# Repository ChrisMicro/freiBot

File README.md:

# freiBot
The freiBot is a very low cost two wheel robot.
The design goal is a robot which is
- easy and fast to build ( 6 hours )
- easy to program ( using an ARDUINO NANO )
- low circuit cost
- usefull for workshops

Here you can see the pictures:

http://roboterclub-freiburg.de/projekte/freibot

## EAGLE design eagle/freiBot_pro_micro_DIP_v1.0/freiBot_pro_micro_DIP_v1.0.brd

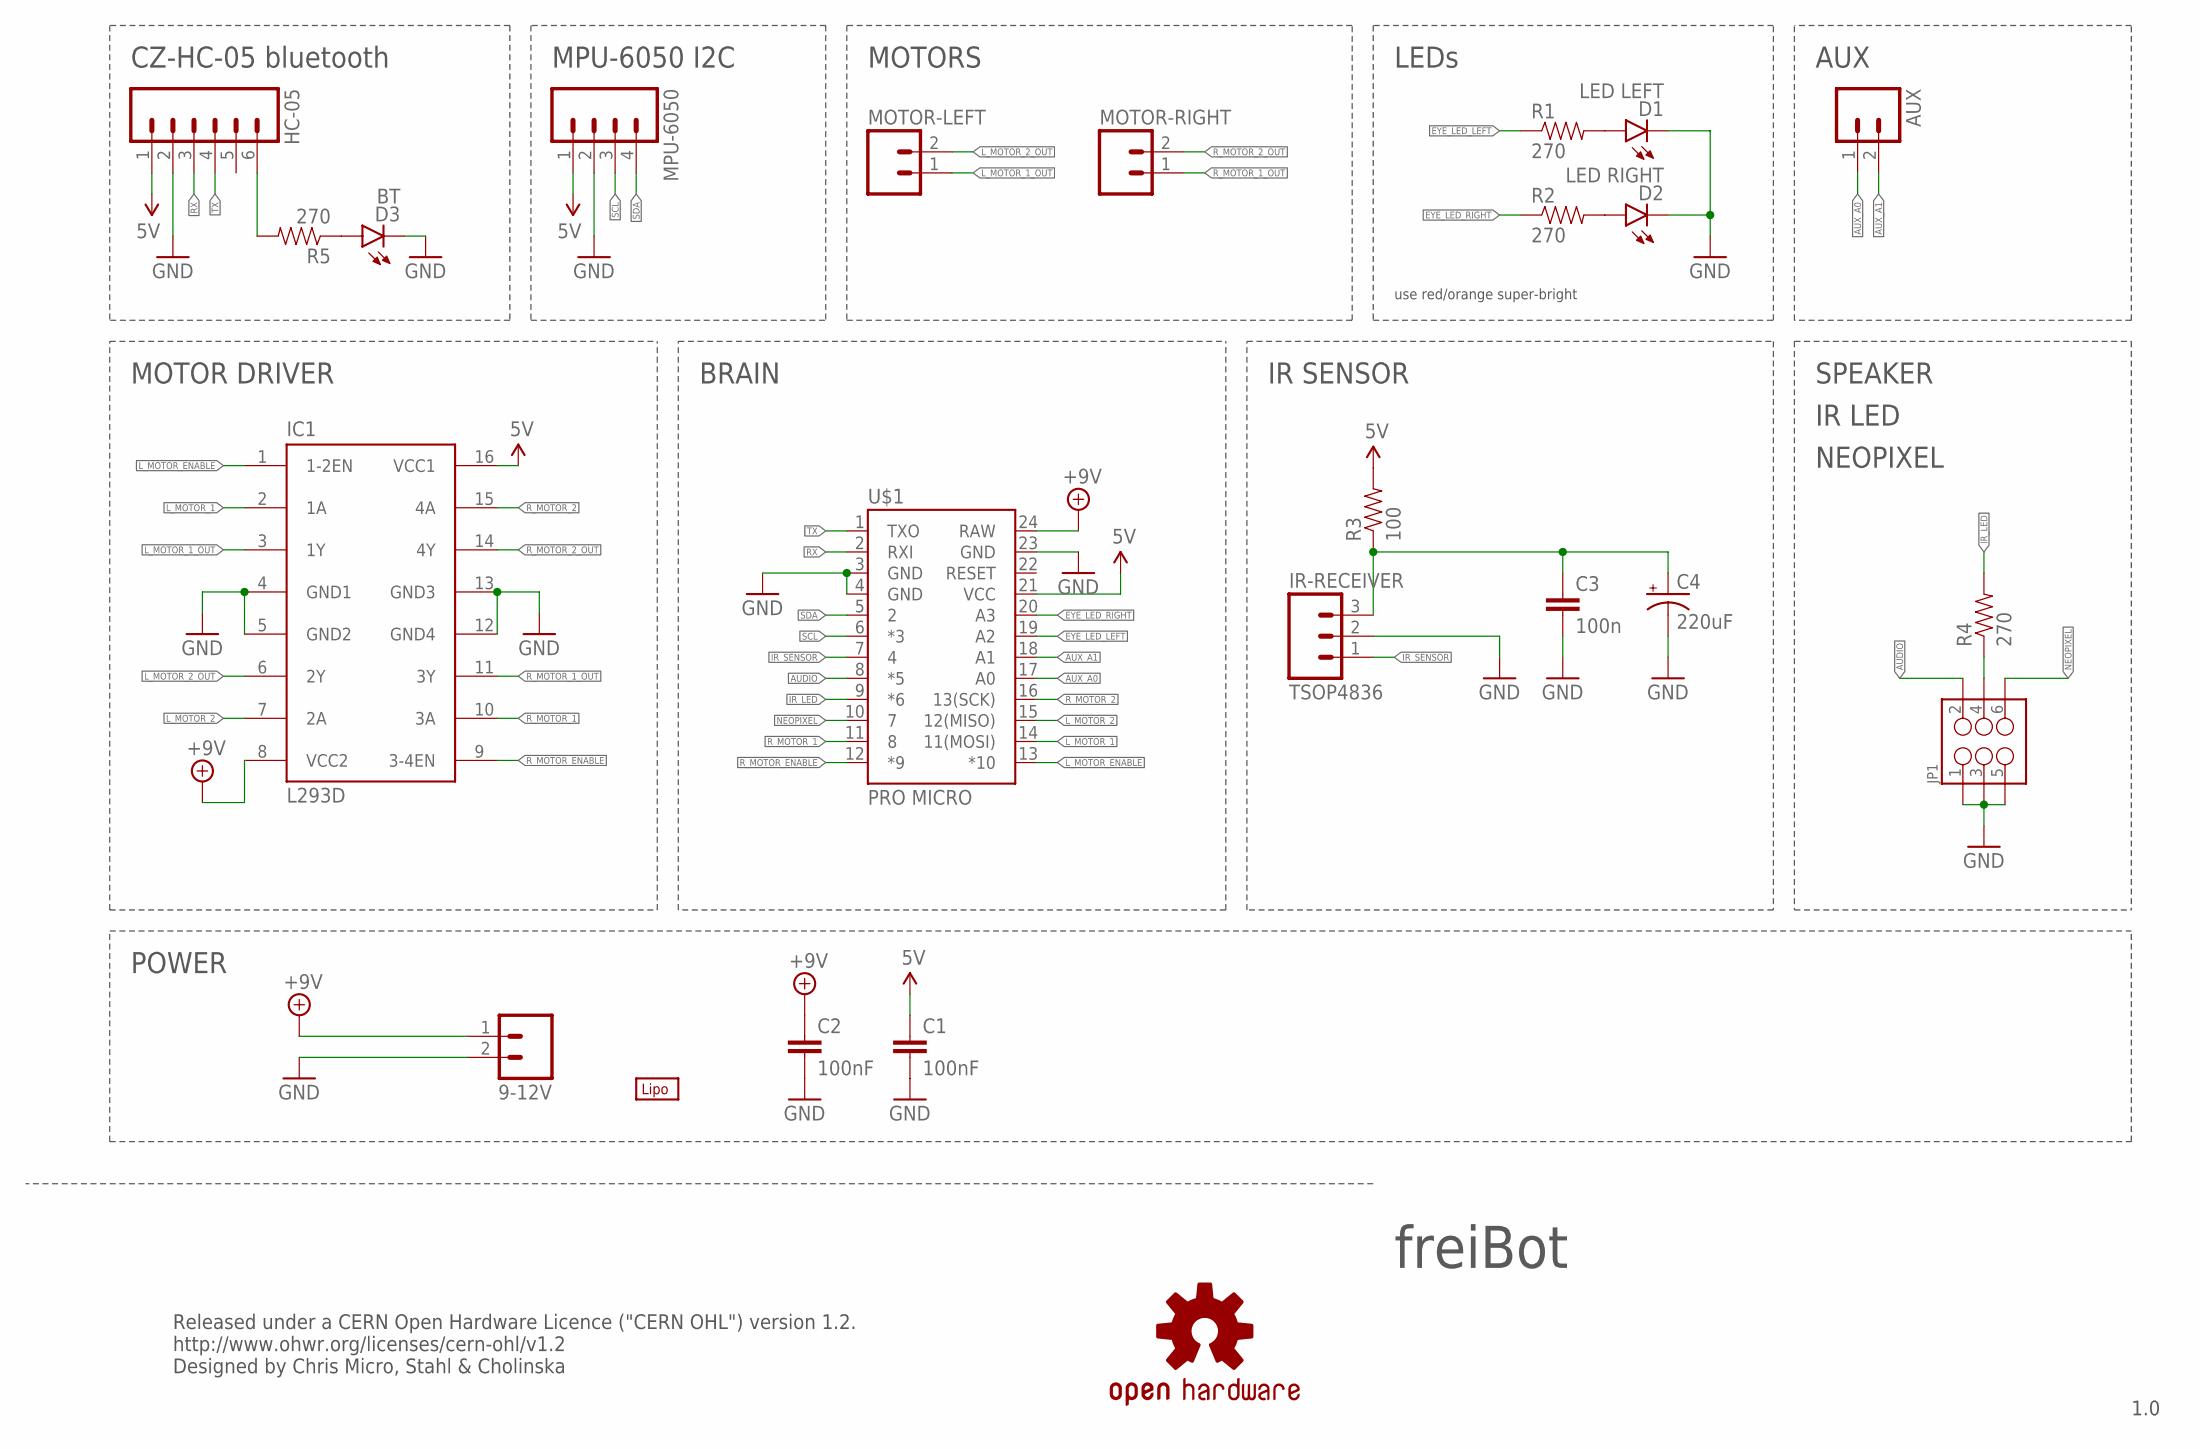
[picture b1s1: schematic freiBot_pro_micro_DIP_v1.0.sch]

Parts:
9-12V: M025MM; SCREWTERMINAL-5MM-2
AUX: M02LOCK_LONGPADS; 1X02_LOCK_LONGPADS
C1, C2: 100nF; CAP-PTH-SMALL-KIT
C3: 100n; CAP-PTH-SMALL-KIT
C4: 220uF; CPOL-RADIAL-100UF-25V
D1: LED LEFT; LED3MM
D2: LED RIGHT; LED3MM
D3: BT; LED3MM
HC-05: M06LONGPADS; 1X06_LONGPADS
IC1: L293D; DIL16
IR-RECEIVER: TSOP4836; 1X03_LONGPADS
JP1: M03X2NO_SILK; 2X3-NS
LOGO1: OSHW-LOGOL-COPPER; OSHW-LOGO-L_COPPER
MOTOR-LEFT: M025MM; SCREWTERMINAL-5MM-2
MOTOR-RIGHT: M025MM; SCREWTERMINAL-5MM-2
MPU-6050: M04LONGPADS; 1X04_LONGPADS
R1, R2, R4, R5: 270; AXIAL-0.3-KIT
R3: 100; AXIAL-0.3-KIT
U$1: PRO MICRO; ARDUINO_PRO_MICRO
U$2: LIPO-OUTLINE2000; LIPO-2000

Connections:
5V: C1.1, HC-05.1, IC1.16 (VCC1), MPU-6050.1, R3.P$2 (2), U$1.21 (VCC)
+9V: 9-12V.1, C2.1, IC1.8 (VCC2), U$1.24 (RAW)
AUDIO: JP1.2, U$1.8 (*5)
AUX_A0: AUX.1, U$1.17 (A0)
AUX_A1: AUX.2, U$1.18 (A1)
EYE_LED_LEFT: R1.P$1 (1), U$1.19 (A2)
EYE_LED_RIGHT: R2.P$1 (1), U$1.20 (A3)
GND: 9-12V.2, C1.2, C2.2, C3.2, C4.2 (-), D1.K (C), D2.K (C), D3.K (C), HC-05.2, IC1.4 (GND1), IC1.5 (GND2), IC1.12 (GND4), IC1.13 (GND3), IR-RECEIVER.2, JP1.1, JP1.3, JP1.5, MPU-6050.2, U$1.3 (GND), U$1.4 (GND), U$1.23 (GND)
IR_LED: R4.P$2 (2), U$1.9 (*6)
IR_SENSOR: IR-RECEIVER.1, U$1.7 (4)
L_MOTOR_1: IC1.2 (1A), U$1.14 (11(MOSI))
L_MOTOR_1_OUT: IC1.3 (1Y), MOTOR-LEFT.1
L_MOTOR_2: IC1.7 (2A), U$1.15 (12(MISO))
L_MOTOR_2_OUT: IC1.6 (2Y), MOTOR-LEFT.2
L_MOTOR_ENABLE: IC1.1 (1-2EN), U$1.13 (*10)
unnamed: D1.A, R1.P$2 (2)
unnamed: D2.A, R2.P$2 (2)
unnamed: D3.A, R5.P$1 (1)
unnamed: JP1.4, R4.P$1 (1)
unnamed: HC-05.6, R5.P$2 (2)
unnamed: C3.1, C4.1 (+), IR-RECEIVER.3, R3.P$1 (1)
NEOPIXEL: JP1.6, U$1.10 (7)
RX: HC-05.3, U$1.2 (RXI)
R_MOTOR_1: IC1.10 (3A), U$1.11 (8)
R_MOTOR_1_OUT: IC1.11 (3Y), MOTOR-RIGHT.1
R_MOTOR_2: IC1.15 (4A), U$1.16 (13(SCK))
R_MOTOR_2_OUT: IC1.14 (4Y), MOTOR-RIGHT.2
R_MOTOR_ENABLE: IC1.9 (3-4EN), U$1.12 (*9)
SCL: MPU-6050.3, U$1.6 (*3)
SDA: MPU-6050.4, U$1.5 (2)
TX: HC-05.4, U$1.1 (TXO)

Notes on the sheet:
IR SENSOR
LEDs
MOTORS
MPU-6050 I2C
MOTOR DRIVER
BRAIN
CZ-HC-05 bluetooth
NEOPIXEL
freiBot
POWER
AUX
SPEAKER
Released under a CERN Open Hardware Licence ("CERN OHL") version 1.2. http://www.ohwr.org/licenses/cern-ohl/v1.2 Designed by Chris Micro, Stahl & Cholinska
1.0
IR LED
use red/orange super-bright

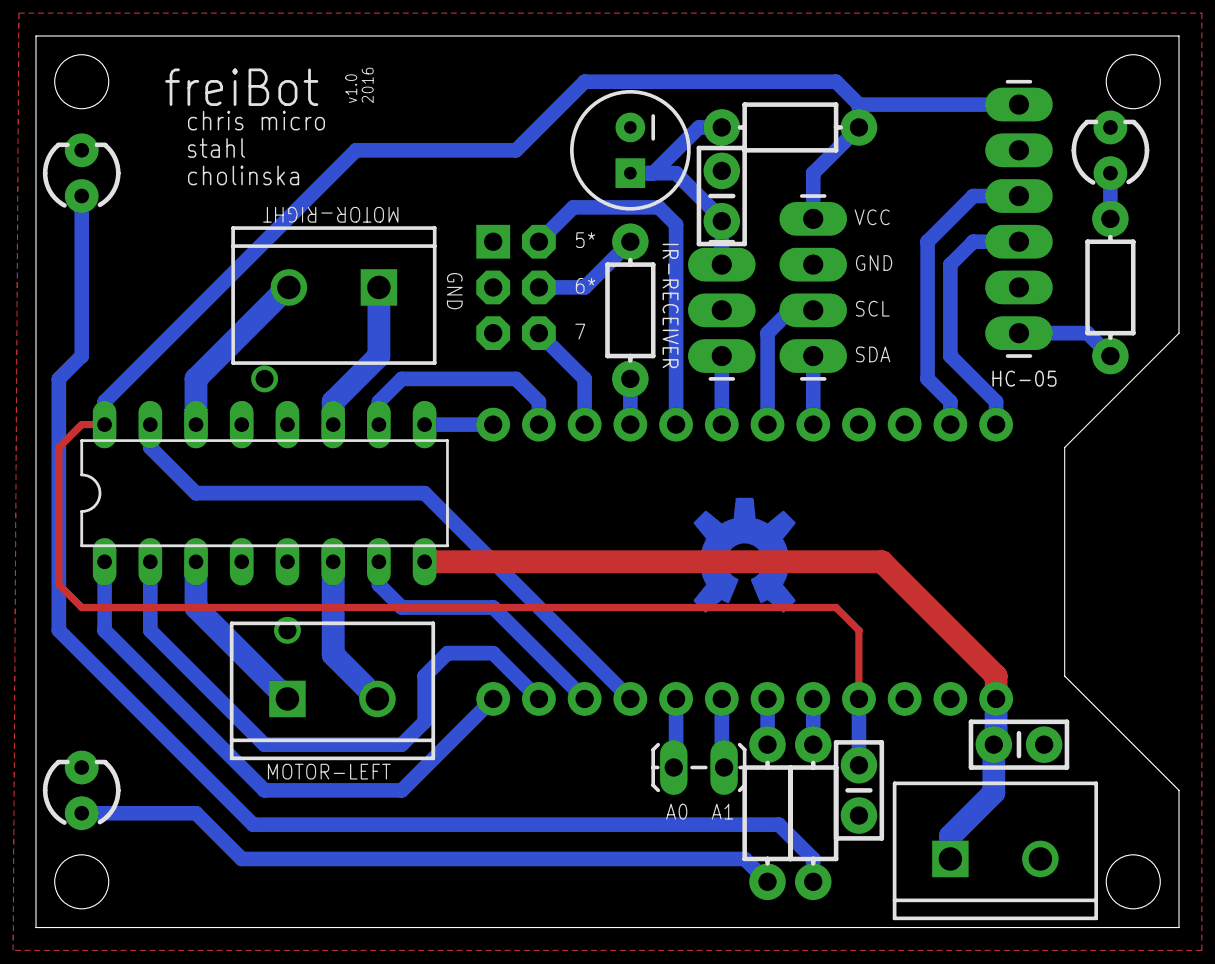
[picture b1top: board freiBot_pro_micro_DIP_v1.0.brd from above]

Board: 2 copper layers, 63.5 x 49.5 mm, 24 parts (1 on the bottom side), 31 nets.

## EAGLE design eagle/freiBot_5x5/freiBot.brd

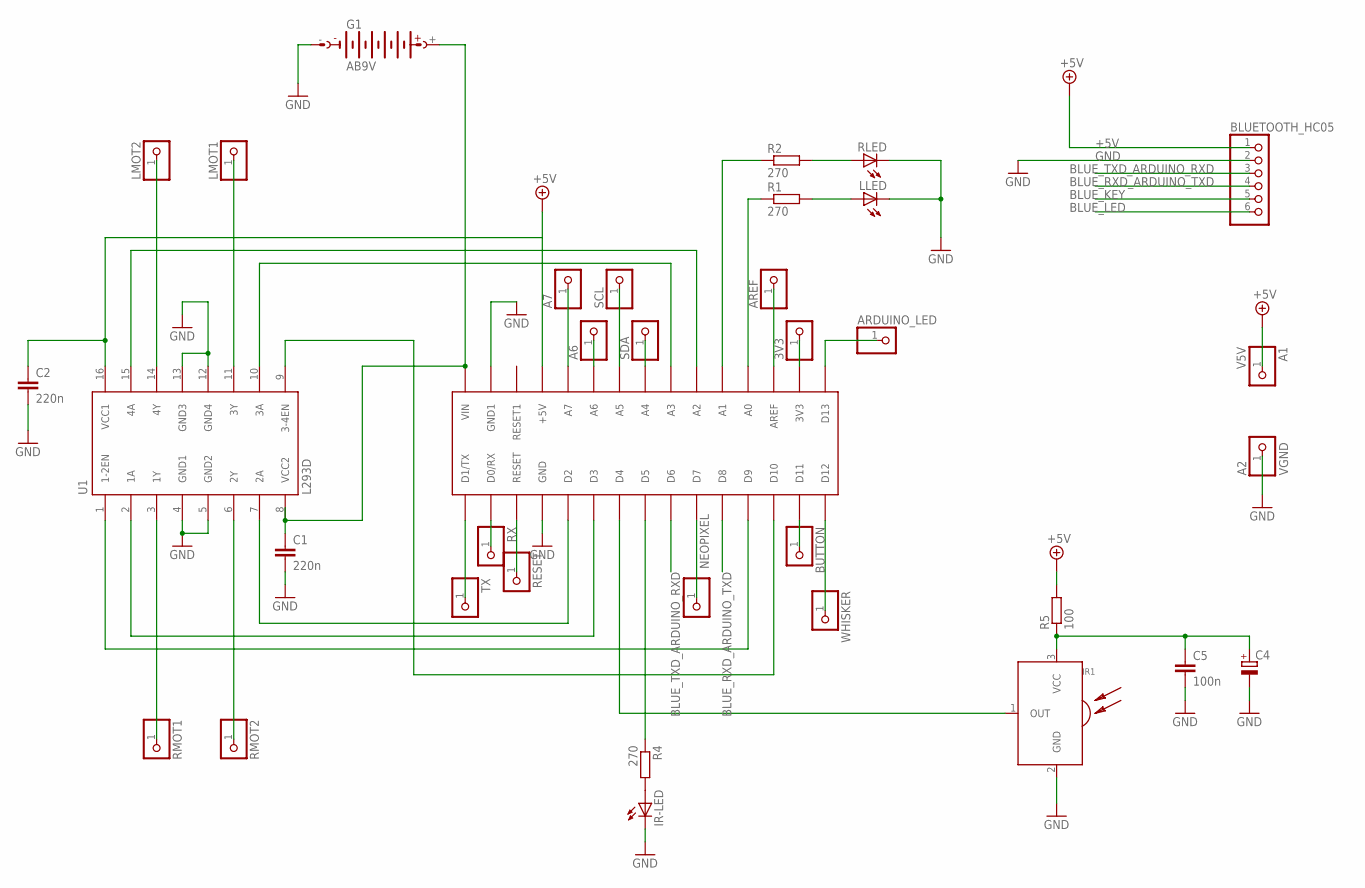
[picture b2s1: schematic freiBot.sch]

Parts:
3V3: PINHD-1X1; 1X01
A1: V5V; 1X01
A2: VGND; 1X01
A6, A7: PINHD-1X1; 1X01
ARDUINO_LED: PINHD-1X1; 1X01
AREF: PINHD-1X1; 1X01
BLUETOOTH_HC05: PINHD-1X6; 1X06
BUTTON: PINHD-1X1; 1X01
C1, C2: 220n; C075-042X103
C4: CPOL-EUE5-8.5; E5-8,5
C5: 100n; C050-025X075
G1: AB9V
IR1: SFH5110; SFH511*
IR-LED: LED5MM
LLED: LED10MM
LMOT1, LMOT2: PINHD-1X1; 1X01
NEOPIXEL: PINHD-1X1; 1X01
R1, R2, R4: 270; 0309/12
R5: 100; 0309/10
RESET: PINHD-1X1; 1X01
RLED: LED10MM
RMOT1, RMOT2: PINHD-1X1; 1X01
RX: PINHD-1X1; 1X01
SCL: PINHD-1X1; 1X01
SDA: PINHD-1X1; 1X01
TX: PINHD-1X1; 1X01
U1: L293D; DIL16
U2: ARDUINONANO; PDIP-32
WHISKER: PINHD-1X1; 1X01

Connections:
+5V: A1.1, BLUETOOTH_HC05.1, C2.1, R5.2, U1.16 (VCC1), U2.+5V
BLUE_KEY: BLUETOOTH_HC05.5
BLUE_LED: BLUETOOTH_HC05.6
BLUE_RXD_ARDUINO_TXD: BLUETOOTH_HC05.4, U2.D8
BLUE_TXD_ARDUINO_RXD: BLUETOOTH_HC05.3, U2.D6
GND: A2.1, BLUETOOTH_HC05.2, C1.2, C2.2, C4.-, C5.2, G1.-, IR1.2 (GND), IR-LED.K (C), LLED.K (C), RLED.K (C), U1.4 (GND1), U1.5 (GND2), U1.12 (GND4), U1.13 (GND3), U2.GND, U2.GND1
unnamed: U1.7 (2A), U2.D2
unnamed: U1.2 (1A), U2.D3
unnamed: U1.1 (1-2EN), U2.D9
unnamed: RMOT1.1, U1.3 (1Y)
unnamed: U1.9 (3-4EN), U2.D10
unnamed: U1.10 (3A), U2.A3
unnamed: U1.15 (4A), U2.A2
unnamed: RMOT2.1, U1.6 (2Y)
unnamed: LMOT1.1, U1.11 (3Y)
unnamed: LMOT2.1, U1.14 (4Y)
unnamed: C1.1, G1.+, U1.8 (VCC2), U2.VIN
unnamed: IR-LED.A, R4.2
unnamed: R1.1, U2.A0
unnamed: R2.1, U2.A1
unnamed: R2.2, RLED.A
unnamed: LLED.A, R1.2
unnamed: SDA.1, U2.A4
unnamed: SCL.1, U2.A5
unnamed: ARDUINO_LED.1, U2.D13
unnamed: U2.D12, WHISKER.1
unnamed: BUTTON.1, U2.D11
unnamed: NEOPIXEL.1, U2.D7
unnamed: IR1.1 (OUT), U2.D4
unnamed: R4.1, U2.D5
unnamed: A6.1, U2.A6
unnamed: 3V3.1, U2.3V3
unnamed: AREF.1, U2.AREF
unnamed: A7.1, U2.A7
unnamed: RESET.1, U2.RESET
unnamed: TX.1, U2.D1/TX
unnamed: RX.1, U2.D0/RX
VCC: C4.+, C5.1, IR1.3 (VCC), R5.1

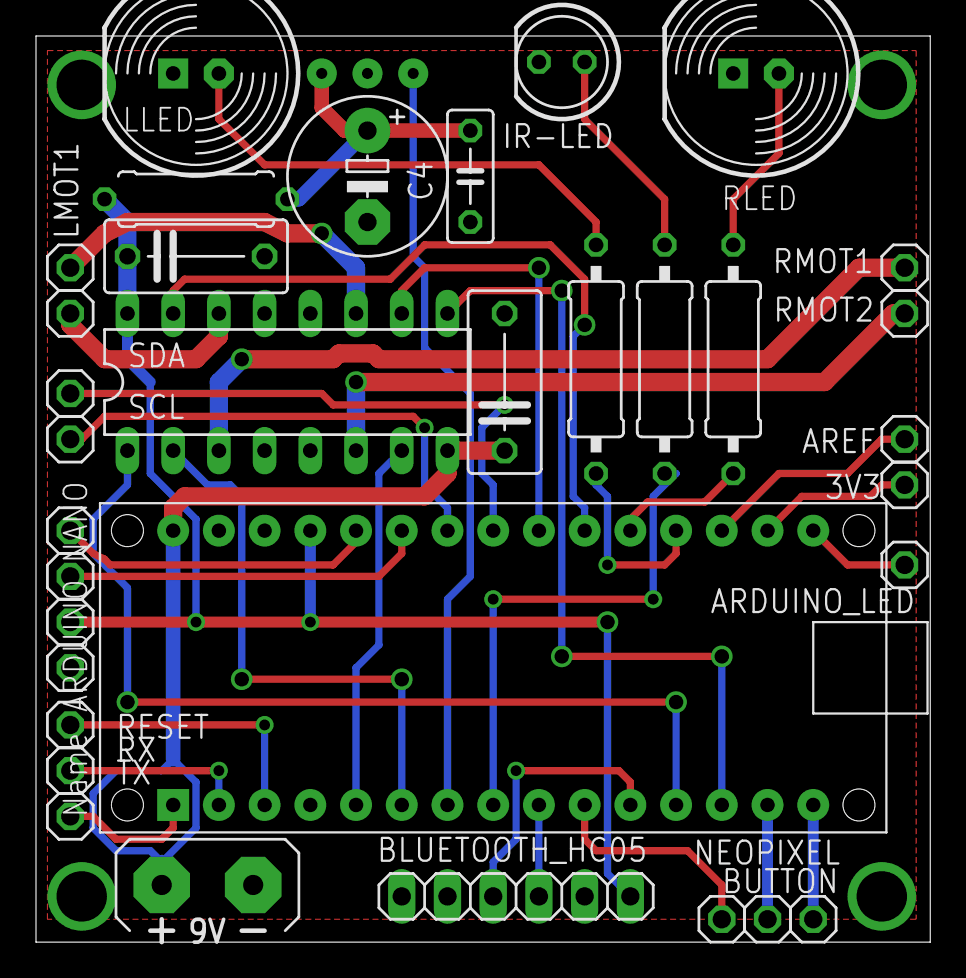
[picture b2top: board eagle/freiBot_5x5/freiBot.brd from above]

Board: 2 copper layers, 49.7 x 50.3 mm, 35 parts (1 on the bottom side), 36 nets.

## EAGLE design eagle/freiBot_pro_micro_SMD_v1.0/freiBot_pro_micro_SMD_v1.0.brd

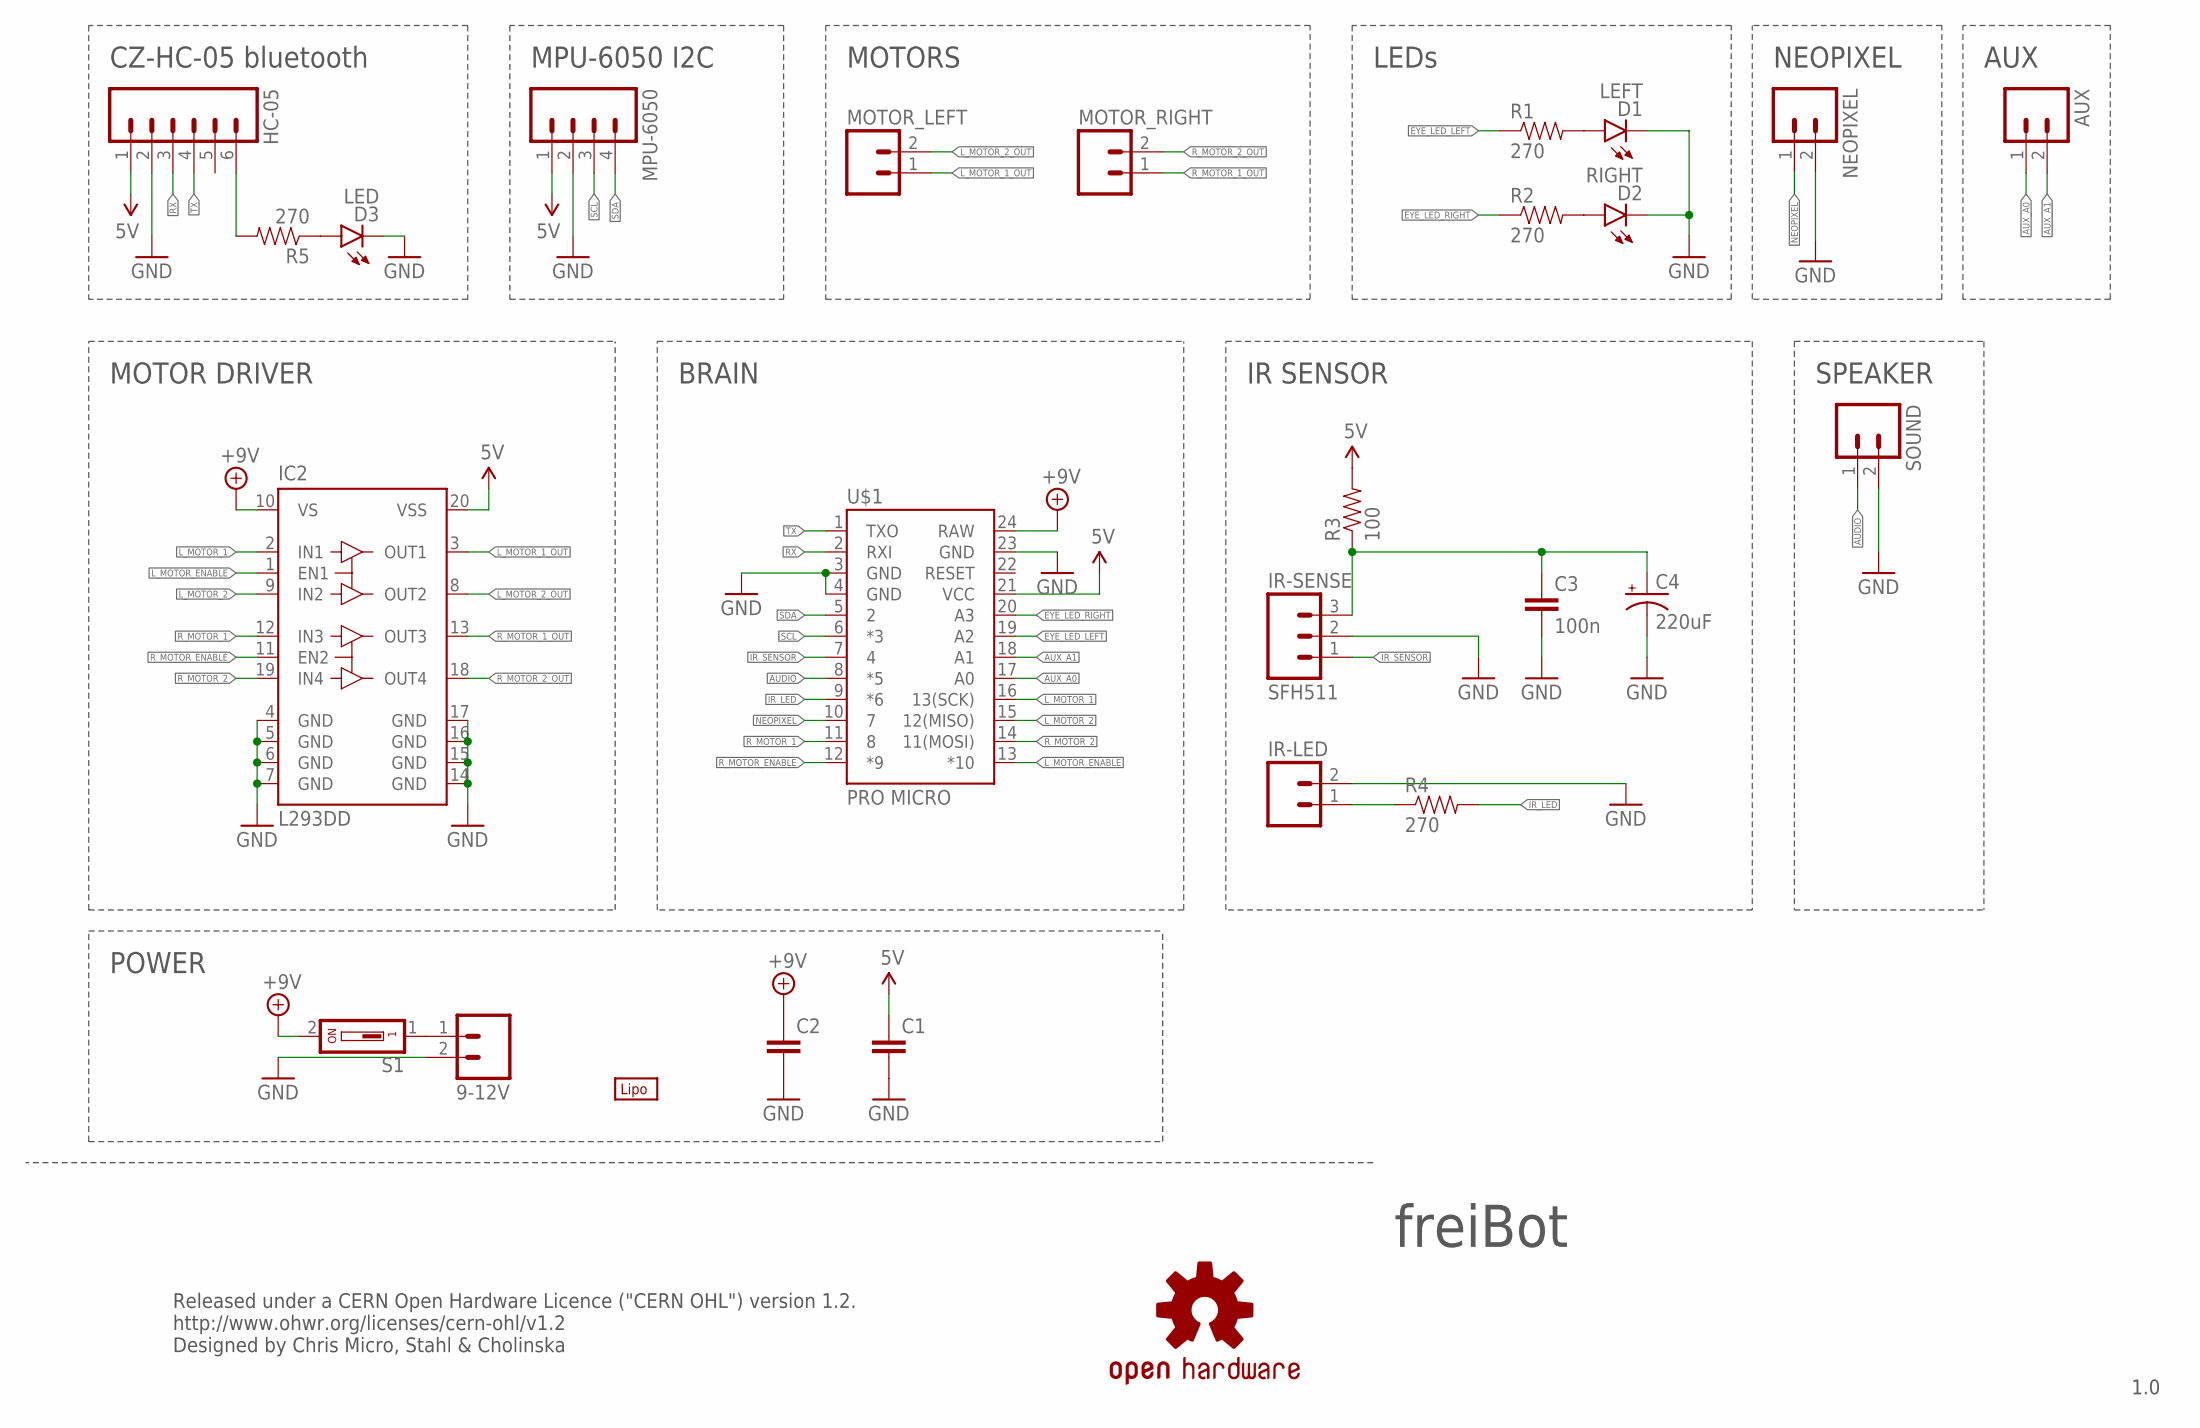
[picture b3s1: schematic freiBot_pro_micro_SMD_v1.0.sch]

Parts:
9-12V: M025MM; SCREWTERMINAL-5MM-2
AUX: M02LOCK_LONGPADS; 1X02_LOCK_LONGPADS
C1, C2: CAP1206; 1206
C3: 100n; 1206
C4: 220uF; EIA3216
D1: LEFT; LED3MM
D2: RIGHT; LED3MM
D3: LED; LED-1206
HC-05: M06LONGPADS; 1X06_LONGPADS
IC2: L293DD; SO20
IR-LED: M02LOCK_LONGPADS; 1X02_LOCK_LONGPADS
IR-SENSE: SFH511; 1X03_LONGPADS
LOGO1: OSHW-LOGOL-COPPER; OSHW-LOGO-L_COPPER
MOTOR_LEFT: M025MM; SCREWTERMINAL-5MM-2
MOTOR_RIGHT: M025MM; SCREWTERMINAL-5MM-2
MPU-6050: M04LONGPADS; 1X04_LONGPADS
NEOPIXEL: M02LOCK_LONGPADS; 1X02_LOCK_LONGPADS
R1, R2, R4, R5: 270; 1206
R3: 100; 1206
S1: SD4-01
SOUND: M02LOCK_LONGPADS; 1X02_LOCK_LONGPADS
U$1: PRO MICRO; ARDUINO_PRO_MICRO
U$2: LIPO-OUTLINE2000; LIPO-2000

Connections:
5V: C1.1, HC-05.1, IC2.20 (VSS), MPU-6050.1, R3.2, U$1.21 (VCC)
+9V: C2.1, IC2.10 (VS), S1.2, U$1.24 (RAW)
AUDIO: SOUND.1, U$1.8 (*5)
AUX_A0: AUX.1, U$1.17 (A0)
AUX_A1: AUX.2, U$1.18 (A1)
EYE_LED_LEFT: R1.1, U$1.19 (A2)
EYE_LED_RIGHT: R2.1, U$1.20 (A3)
GND: 9-12V.2, C1.2, C2.2, C3.2, C4.C (-), D1.K (C), D2.K (C), D3.C, HC-05.2, IC2.4 (GND), IC2.5 (GND), IC2.6 (GND), IC2.7 (GND), IC2.14 (GND), IC2.15 (GND), IC2.16 (GND), IC2.17 (GND), IR-LED.2, IR-SENSE.2, MPU-6050.2, NEOPIXEL.2, SOUND.2, U$1.3 (GND), U$1.4 (GND), U$1.23 (GND)
IR_LED: R4.2, U$1.9 (*6)
IR_SENSOR: IR-SENSE.1, U$1.7 (4)
L_MOTOR_1: IC2.2 (IN1), U$1.16 (13(SCK))
L_MOTOR_1_OUT: IC2.3 (OUT1), MOTOR_LEFT.1
L_MOTOR_2: IC2.9 (IN2), U$1.15 (12(MISO))
L_MOTOR_2_OUT: IC2.8 (OUT2), MOTOR_LEFT.2
L_MOTOR_ENABLE: IC2.1 (EN1), U$1.13 (*10)
unnamed: D1.A, R1.2
unnamed: D2.A, R2.2
unnamed: D3.A, R5.1
unnamed: IR-LED.1, R4.1
unnamed: HC-05.6, R5.2
unnamed: C3.1, C4.A (+), IR-SENSE.3, R3.1
unnamed: 9-12V.1, S1.1
NEOPIXEL: NEOPIXEL.1, U$1.10 (7)
RX: HC-05.3, U$1.2 (RXI)
R_MOTOR_1: IC2.12 (IN3), U$1.11 (8)
R_MOTOR_1_OUT: IC2.13 (OUT3), MOTOR_RIGHT.1
R_MOTOR_2: IC2.19 (IN4), U$1.14 (11(MOSI))
R_MOTOR_2_OUT: IC2.18 (OUT4), MOTOR_RIGHT.2
R_MOTOR_ENABLE: IC2.11 (EN2), U$1.12 (*9)
SCL: MPU-6050.3, U$1.6 (*3)
SDA: MPU-6050.4, U$1.5 (2)
TX: HC-05.4, U$1.1 (TXO)

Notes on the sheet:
IR SENSOR
LEDs
MOTORS
MPU-6050 I2C
MOTOR DRIVER
BRAIN
CZ-HC-05 bluetooth
NEOPIXEL
freiBot
POWER
AUX
SPEAKER
Released under a CERN Open Hardware Licence ("CERN OHL") version 1.2. http://www.ohwr.org/licenses/cern-ohl/v1.2 Designed by Chris Micro, Stahl & Cholinska
1.0

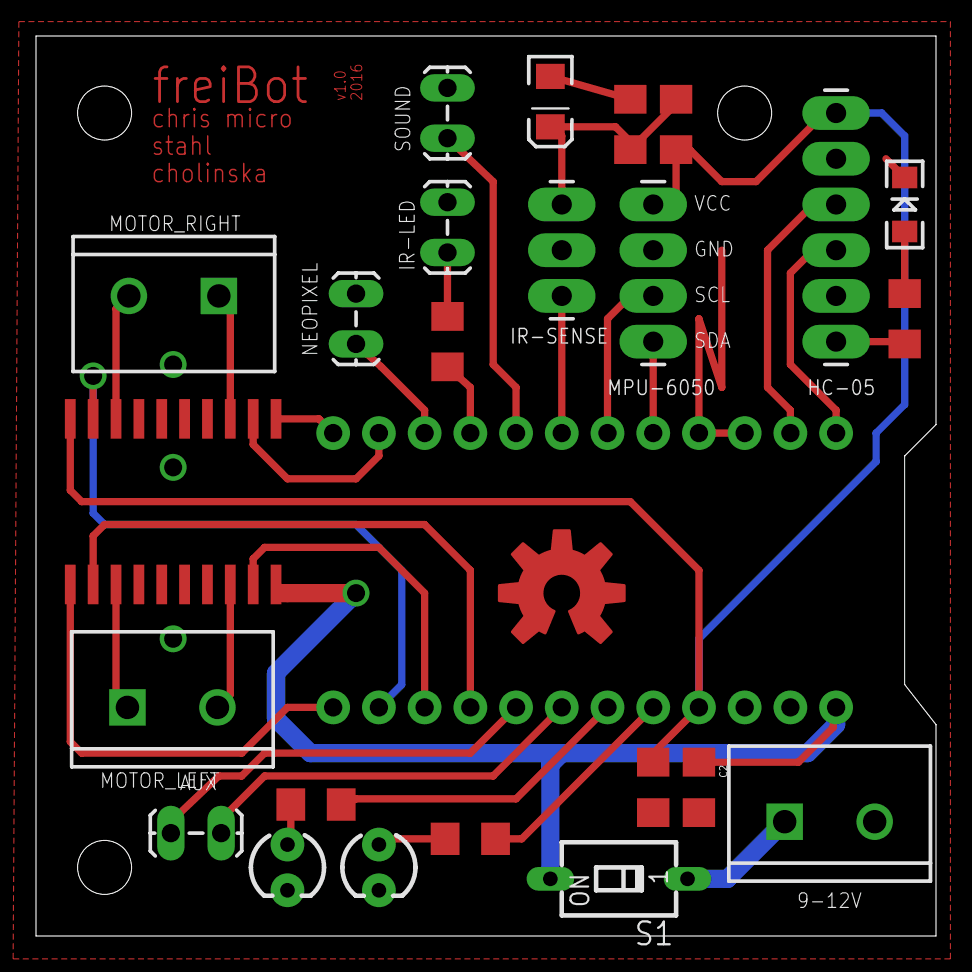
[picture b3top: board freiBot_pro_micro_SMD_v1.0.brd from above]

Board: 2 copper layers, 50.0 x 50.0 mm, 27 parts (0 on the bottom side), 32 nets.

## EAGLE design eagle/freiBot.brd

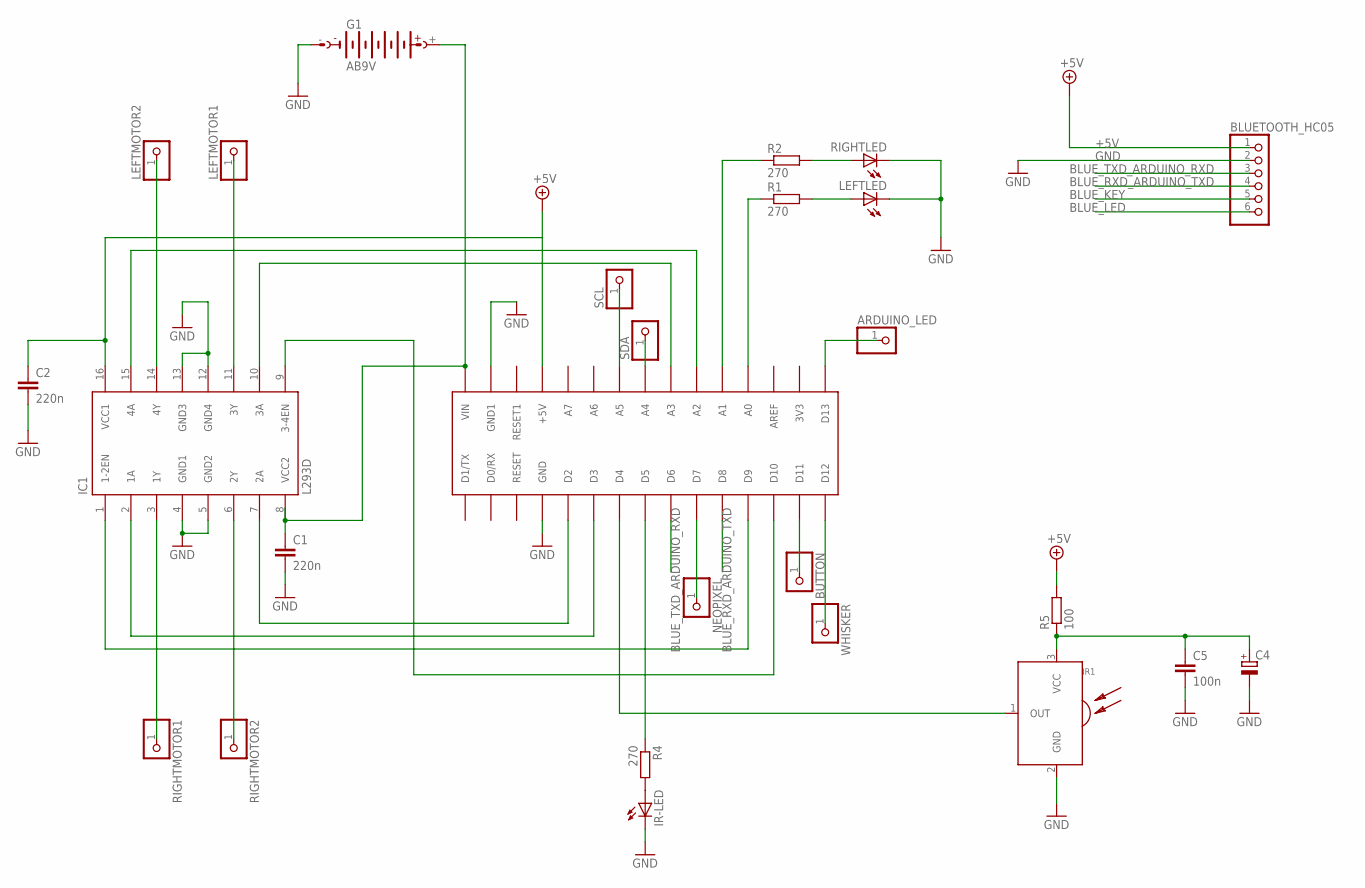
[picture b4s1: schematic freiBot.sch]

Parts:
ARDUINO_LED: PINHD-1X1; 1X01
BLUETOOTH_HC05: PINHD-1X6; 1X06
BUTTON: PINHD-1X1; 1X01
C1, C2: 220n; C075-042X103
C4: CPOL-EUE5-8.5; E5-8,5
C5: 100n; C050-025X075
G1: AB9V
IC1: L293D; DIL16
IR1: SFH5110; SFH511*
IR-LED: LED5MM
LEFTLED: LED10MM
LEFTMOTOR1, LEFTMOTOR2: PINHD-1X1; 1X01
NEOPIXEL: PINHD-1X1; 1X01
R1, R2, R4: 270; 0309/12
R5: 100; 0309/10
RIGHTLED: LED10MM
RIGHTMOTOR1, RIGHTMOTOR2: PINHD-1X1; 1X01
SCL: PINHD-1X1; 1X01
SDA: PINHD-1X1; 1X01
U$1: ARDUINONANO; PDIP-32
WHISKER: PINHD-1X1; 1X01

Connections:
+5V: BLUETOOTH_HC05.1, C2.1, IC1.16 (VCC1), R5.2, U$1.+5V
BLUE_KEY: BLUETOOTH_HC05.5
BLUE_LED: BLUETOOTH_HC05.6
BLUE_RXD_ARDUINO_TXD: BLUETOOTH_HC05.4, U$1.D8
BLUE_TXD_ARDUINO_RXD: BLUETOOTH_HC05.3, U$1.D6
GND: BLUETOOTH_HC05.2, C1.2, C2.2, C4.-, C5.2, G1.-, IC1.4 (GND1), IC1.5 (GND2), IC1.12 (GND4), IC1.13 (GND3), IR1.2 (GND), IR-LED.K (C), LEFTLED.K (C), RIGHTLED.K (C), U$1.GND, U$1.GND1
unnamed: IC1.7 (2A), U$1.D2
unnamed: IC1.2 (1A), U$1.D3
unnamed: IC1.1 (1-2EN), U$1.D9
unnamed: IC1.3 (1Y), RIGHTMOTOR1.1
unnamed: IC1.9 (3-4EN), U$1.D10
unnamed: IC1.10 (3A), U$1.A3
unnamed: IC1.15 (4A), U$1.A2
unnamed: IC1.6 (2Y), RIGHTMOTOR2.1
unnamed: IC1.11 (3Y), LEFTMOTOR1.1
unnamed: IC1.14 (4Y), LEFTMOTOR2.1
unnamed: C1.1, G1.+, IC1.8 (VCC2), U$1.VIN
unnamed: IR-LED.A, R4.2
unnamed: R1.1, U$1.A0
unnamed: R2.1, U$1.A1
unnamed: R2.2, RIGHTLED.A
unnamed: LEFTLED.A, R1.2
unnamed: SDA.1, U$1.A4
unnamed: SCL.1, U$1.A5
unnamed: ARDUINO_LED.1, U$1.D13
unnamed: U$1.D12, WHISKER.1
unnamed: BUTTON.1, U$1.D11
unnamed: NEOPIXEL.1, U$1.D7
unnamed: IR1.1 (OUT), U$1.D4
unnamed: R4.1, U$1.D5
VCC: C4.+, C5.1, IR1.3 (VCC), R5.1

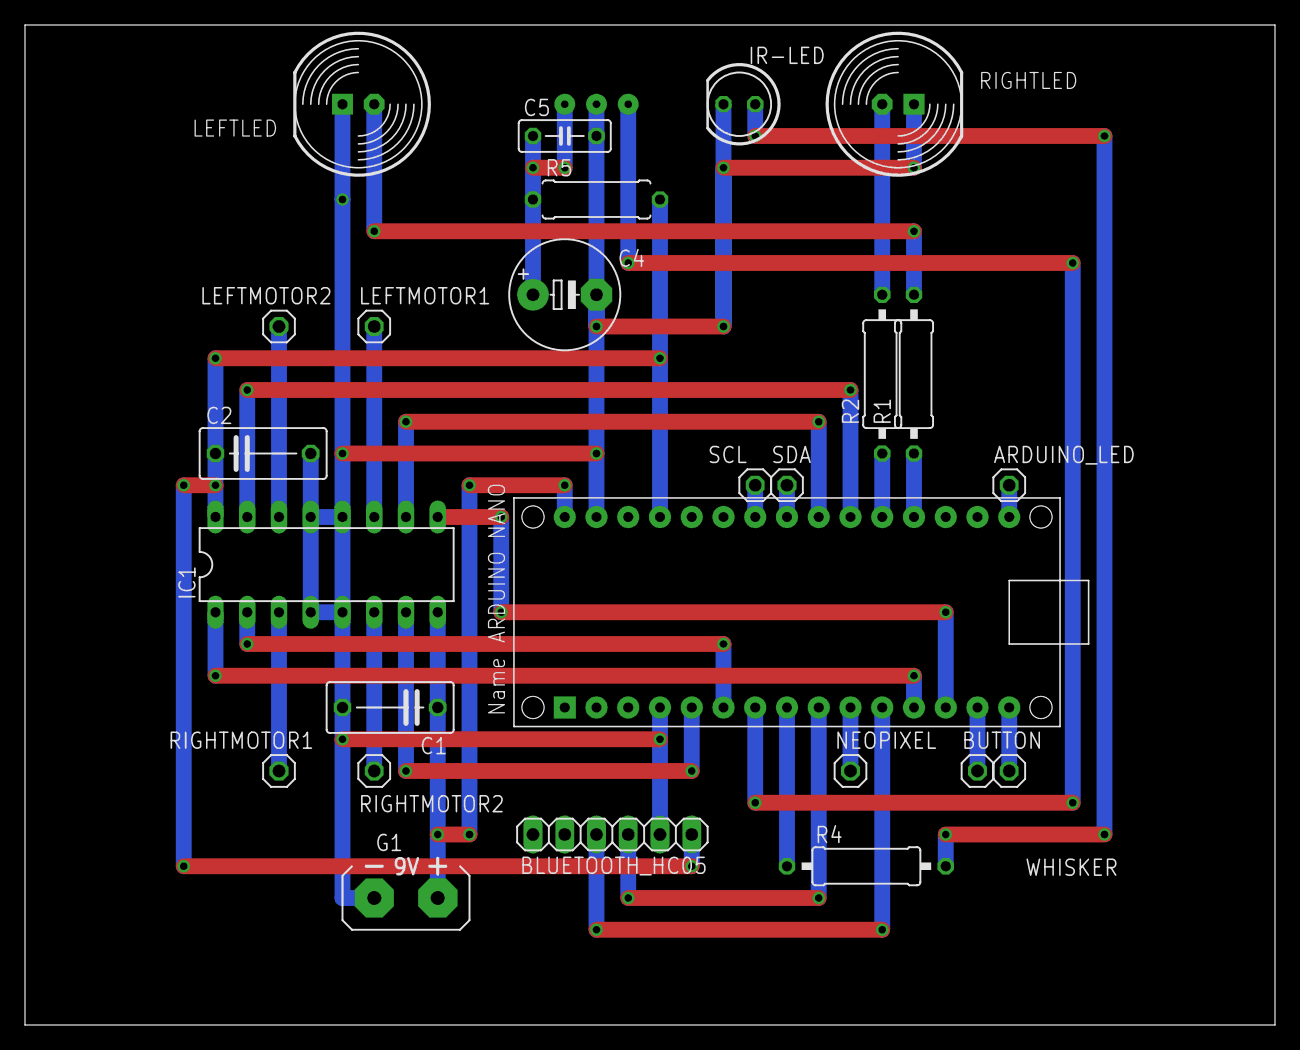
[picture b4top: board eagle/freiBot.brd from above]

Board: 2 copper layers, 100.0 x 80.0 mm, 26 parts (1 on the bottom side), 29 nets.

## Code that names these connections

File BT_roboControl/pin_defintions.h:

/*************************************************************************************

  GENUBOT 

  robot hardware:

  microcontroller:     Arduino Nano
  motor driver:        L293D
  motors:              Pollin motors 
  wheels:              inline skate ball bearings
  
  sensors:
  - button
  - 1 whisker 
  - 2 LEDs ( used as light sensor )
  - MPU6050 3 axis accelerometer/gyrometer 
  - IR sensor SFH5110

************************************************************************************/

// Arduino Nano pin out and schematic:
// https://www.arduino.cc/en/uploads/Main/ArduinoNanoManual23.pdf

// connecting the ARDUINO Nano and the MPU6050 accelerometer:
// http://shirotsuku.sakura.ne.jp/blog/?p=442
// ( interrupt pin is not connected at the moment to genubot )

// net list:
//===== robot pin name =  ARDUINO pin ===============================================================
#define MOTOR_RIGHT1           2 // dout, L293D pin10, motor driver right side, half bridge 1
#define MOTOR_RIGHT2           3 // dout, L293D pin15, motor driver right side, half bridge 2
#define IR_SENSOR              4  // din , SFH5110 sensor ( signal is active low )
#define BLUE_TXD_ARDUINO_RXD   6  // din, bluetooth hc05 modul 
#define NEOPIXEL_PIN           7  // dout, WS2812 RGB LED controll pin
#define BLUE_RXD_ARDUINO_TXD   8  // dout, bluetooth hc05 modul 
#define ENABLE_RIGHT           9  // dout, L293D pin1, motor driver enable pin for right motor, OC1B used for motor PWM
#define ENABLE_LEFT           10 // dout, L293D pin9, motor driver enable pin for left moter, OC1A used for motor PWM
#define BUTTONPIN             11 // din,  button ( configure with pull up )
#define WHISKERPIN            12 // din,  whisker ( like a button configure with pull up )
#define LEDPIN                13 // dout, ARDUINO NANO LED 

#define EYE_LED_LEFT     A0 // dout,ain, LED or LED as light sensor
#define EYE_LED_RIGHT    A1 // dout,ain, LED or LED as light sensor
#define MOTOR_LEFT2      A2  // dout, L293D pin2, motor driver left side half bridge 2
#define MOTOR_LEFT1      A3  // dout, L293D pin7, motor driver left side half bridge 1

// A2
// A3
#define I2C_SDA_PIN      A4 // I2C SDA, connected to MPU6050
#define I2C_SCL_PIN      A5 // I2C SCL, connected to MPU6050
// A6
// A7

// tbd:
// IR-LED digital out for distance sensor
// digital input for second whisker
// CNY70 line sensor digital out for LED
// CNY70 line sensor digital in for sensor

/*******************************************************************************
*   -c--date---version--nickname--------email---------------------------------
*
*   (c) 2015   V0.1     stochri         christoph(at)roboterclub-freiburg.de
*   (c) ..     V0.2     ...... ........ ( your name ) ........................
*
*******************************************************************************
*   This program is free software; you can redistribute it and/or modify      *
*   it under the terms of the GNU General Public License as published by      *
*   the Free Software Foundation version 2 of the License,                    *
*   If you want to use this software for commercial purposes and you          *
*   don't want to make it open source, please contact the authors for         *
*   licensing.                                                                *
*                                                                             *
*   IF YOU EXTEND THE PROGRAM PLEASE MAINTAIN THE LIST OF AUTHORS             *
*   ( which means adding copyright in the list above )                        *
*                                                                             *
*******************************************************************************/

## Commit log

2015-08-09 initial version!
2015-08-09 Asuro compatibility functions added
2015-08-09 Asuro functions separated
2015-08-09 Kooperative Multitasking with Semaphore
2015-08-09 whisker drive back added
2015-08-28 eye leds added
2015-08-29 eye leds as light sensor
2015-08-29 accelaration sensor test added
2015-09-11 ir sensor added
2015-09-12 genubot net list extended
2015-09-13 genuBot functions added
2015-09-13 TodoList architecture first version
2015-09-13 whisker detection improved
2015-09-18 Example_ToneMelody added
2015-09-18 Example_readLightSensors added
2015-09-18 Example_lightSensorsBeep added
2015-09-19 motor examples added
2015-10-02 TEST folders added
2015-10-02 TEST folders now realy added
2015-10-02 TEST_motor added
2015-10-02 motor pins corrected
2015-10-03 copyright text added
2015-10-09 pins corrected in TEST_motor_lowestLevel
2015-10-09 sound functions repaired
2015-10-09 freiBot libs updated
2015-10-09 schematic added
2015-10-12 programs of Tormod added
2015-10-17 motor free corrected in EXPERIMENTAL_sidewalk
2015-10-17 ligth jump detection added
2015-10-17 MPU6050_test renamed
2015-10-17 TEST_MPU6050 forgotten to add
2015-10-17 wait for light beep corrected
2015-10-17 waitForLightRattle added
2015-10-17 appregio added
2015-10-17 random sound pentatonic added
2015-10-18 line follow not working yet
2015-10-23 openscad design files added
2015-10-23 ball bearing dimensions added
2015-10-23 radio control example added
2015-10-25 eagle schematic added
2015-10-28 SGMK pneu added
2015-10-29 IrDistance added
2015-12-16 freibot_pnew now with hub. It does not need a ball bearing any more
2015-12-17 motor model added
2015-12-18 motor holder added
2015-12-19 circuit board holder added
2015-12-19 axis bearings added
2015-12-19 main base plate with all components added
2015-12-19 front size minimized, it was to big to print
2015-12-20 freibot rubber band wheel added
2015-12-21 fitting of motor holder improved, dual bearing base plate added
2015-12-24 new eagle schematic
2015-12-25 additional parts added
2015-12-29 light sensor graph with less swing
2015-12-30 fast adc sample added
2015-12-31 ignore temporary files
2015-12-31 light sensor detection improved
2015-12-31 removed temp files
2015-12-31 added new micro examples with updated pin definitions (work in progress)
2015-12-31 born
2015-12-31 turn to light light seeker added
2016-01-02 grundplatte lurch from cholinska added
2016-01-04 bluetooth modul hc05 connection added
2016-01-04 bluetooth remote control added
2016-01-10 additional pins in schematic added
2016-01-10 manually routed pcb for manual etching added
2016-01-10 added pcb prototype for pro micro version
2016-01-11 Laserfile Grundplatte 4mm Design "Vampir"
2016-01-18 pdf für grundplatte vampir
2016-02-21 updated pin definitions to match the smd prototype board
2016-02-21 removed svg, pdf works better in inkscape
2016-04-08 DIP version of freiBot (pro micro)
2016-04-15 Alejandro's 5x5 board
2016-04-17 added cam job and masks
2016-04-17 added comment for leds
2016-09-19 README updated
2017-11-28 TRobot
2017-12-03 sliderServo added
2017-12-03 gui example added
2017-12-03 random and sine servo added
2017-12-03 sineServo_x2 added
2017-12-04 two speed servo added
2017-12-07 some more examples
2017-12-07 dingDongGenerator added
2017-12-30 robot.bas added

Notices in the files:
parts and their libraries:
SparkFun-Capacitors: Licensing: Creative Commons ShareAlike 4.0 International - https://creativecommons.org/licenses/by-sa/4.0
